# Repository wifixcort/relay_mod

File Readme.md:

#Single relay module

Relay module for arduino.
Input signal 5v
Relay 125VAC@10A
NO-COM-NC

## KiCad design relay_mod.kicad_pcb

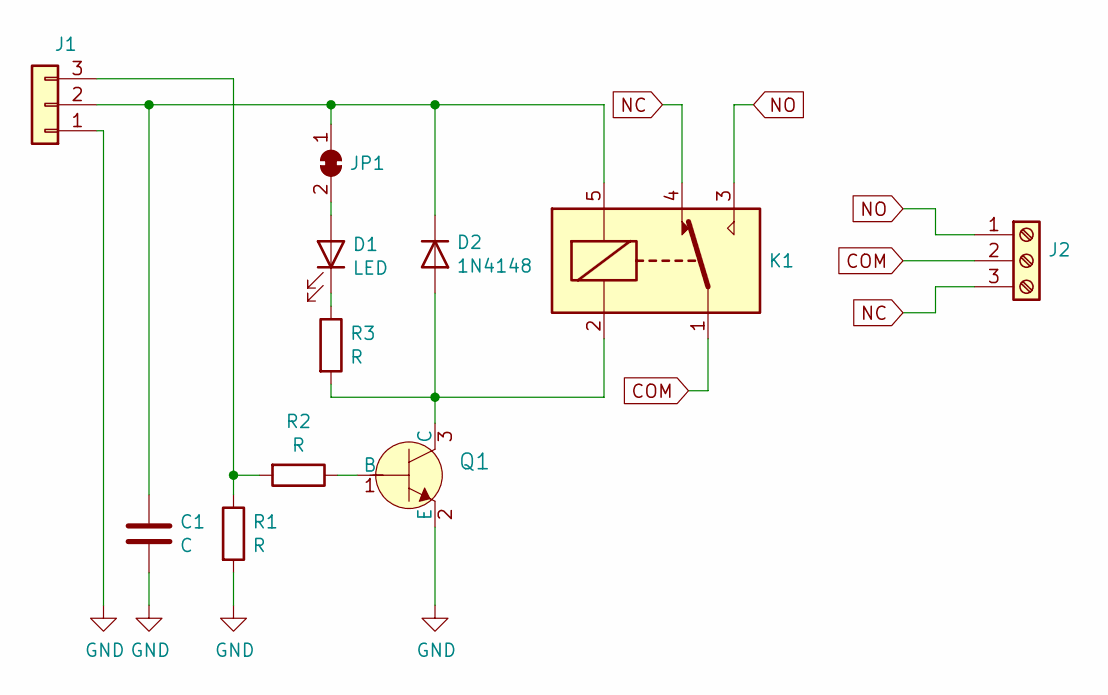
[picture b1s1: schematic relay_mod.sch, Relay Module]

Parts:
C1: C; C_0805_2012Metric_Pad1.15x1.40mm_HandSolder
D1: LED; LED_0805_2012Metric_Pad1.15x1.40mm_HandSolder
D2: 1N4148; D_SOD-123
J1: Conn_01x03; PinHeader_1x03_P2.54mm_Vertical
J2: Screw_Terminal_01x03; TerminalBlock_Phoenix_PT-1,5-3-5.0-H_1x03_P5.00mm_Horizontal
JP1: SolderJumper_2_Bridged; SolderJumper-2_P1.3mm_Bridged2Bar_RoundedPad1.0x1.5mm
K1: SANYOU_SRD_Form_C; Relay_SPDT_SANYOU_SRD_Series_Form_C
Q1: MMSS8050-H-TP; SOT-23-3; MPN MMSS8050-H-TP; Digi-Key_PN MMSS8050-H-TPMSCT-ND
R1, R2, R3: R; R_0805_2012Metric_Pad1.15x1.40mm_HandSolder

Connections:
COM: J2.2, K1.1
GND: C1.2, J1.1, Q1.2 (E), R1.2
NC: J2.3, K1.4
NO: J2.1, K1.3
unnamed: C1.1, D2.1 (K), J1.2, JP1.1 (A), K1.5
unnamed: D1.1 (K), R3.1
unnamed: D1.2 (A), JP1.2 (B)
unnamed: D2.2 (A), K1.2, Q1.3 (C), R3.2
unnamed: J1.3, R1.1, R2.2
unnamed: Q1.1 (B), R2.1

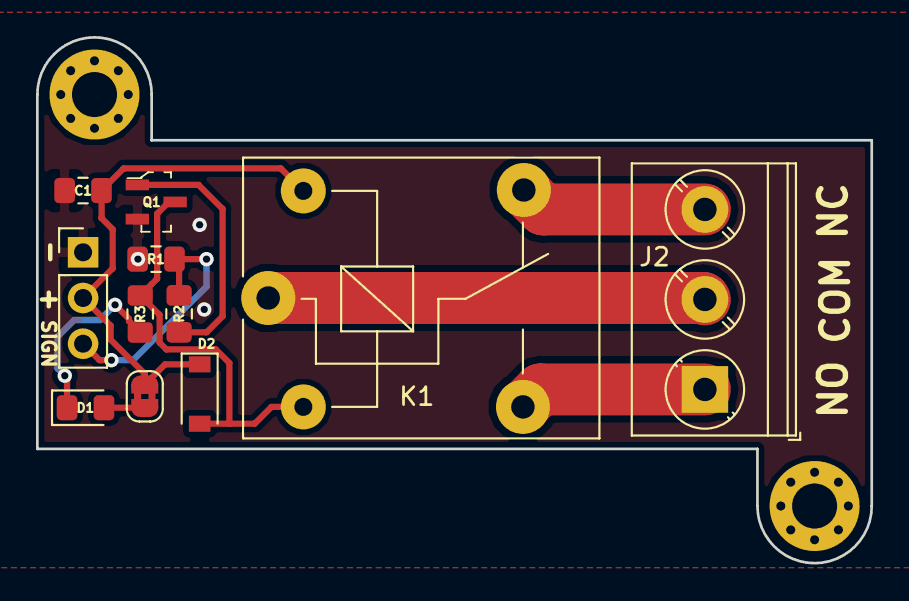
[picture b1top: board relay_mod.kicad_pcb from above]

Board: 2 copper layers, 46.4 x 29.2 mm, 12 parts (1 on the bottom side), 10 nets.

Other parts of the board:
OSHW_Mono_0.1_Scale: CR00001; OSHW_Mono_0.1_Scale

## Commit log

2020-07-22 Relay board for arduino
2020-07-22 screenshots of this relay board
2020-07-22 Licence and Readme added
2020-07-22 Made in Costa Rica
2020-09-12 License change to CERN lic v2
2020-11-05 Adding oshwa cert
2020-11-06 Cert image file
2020-11-06 Readme LIC update
